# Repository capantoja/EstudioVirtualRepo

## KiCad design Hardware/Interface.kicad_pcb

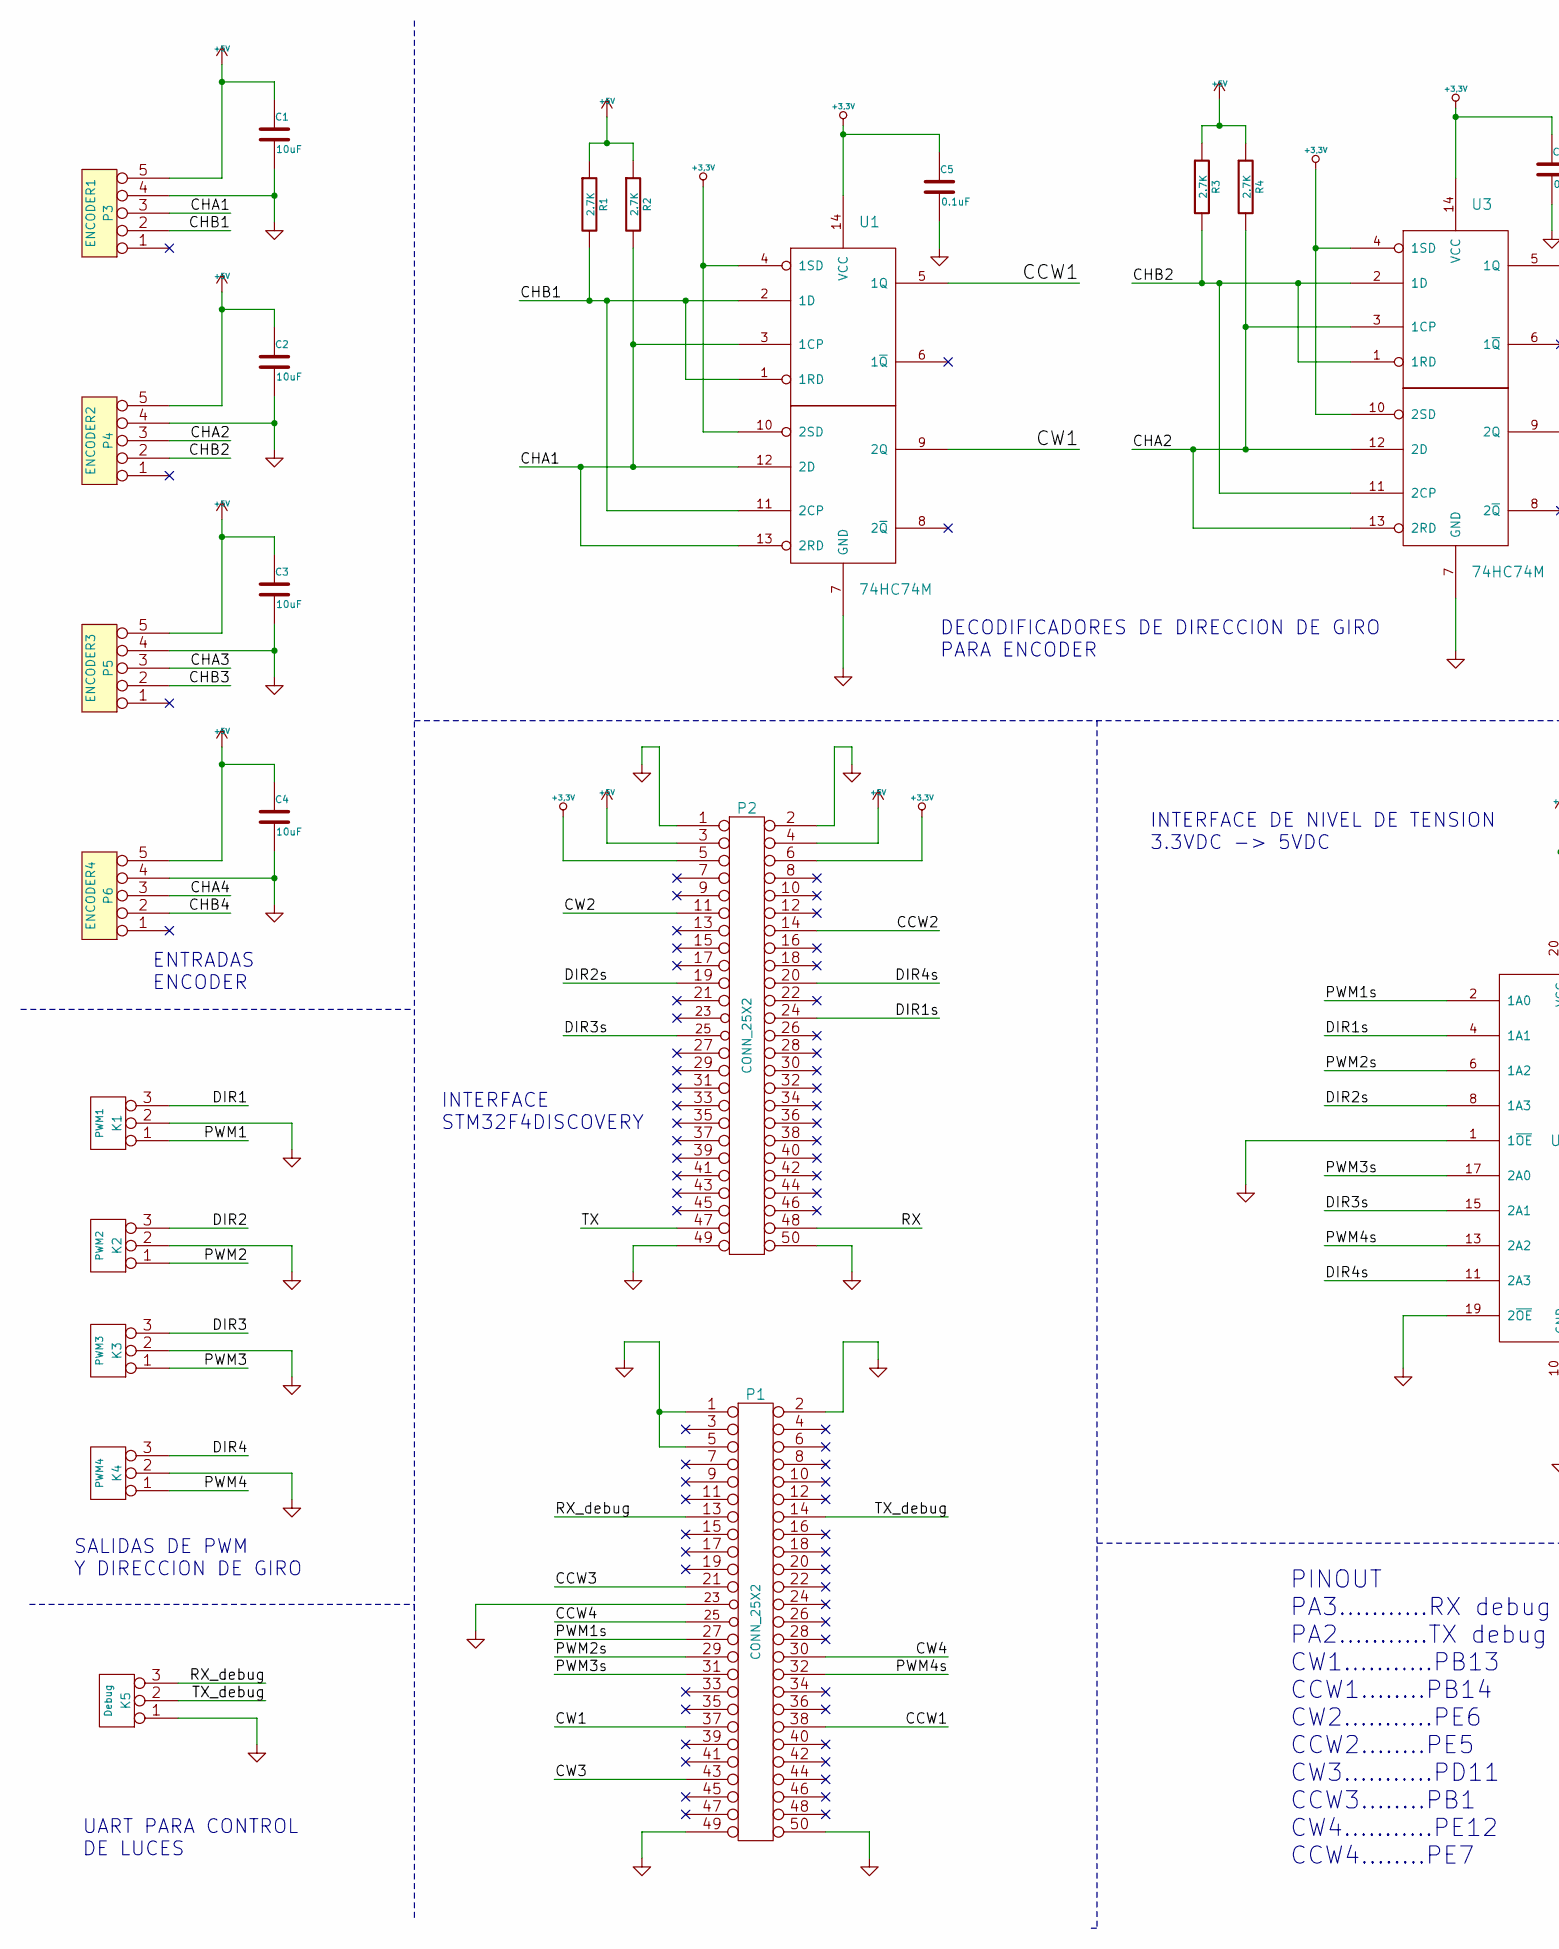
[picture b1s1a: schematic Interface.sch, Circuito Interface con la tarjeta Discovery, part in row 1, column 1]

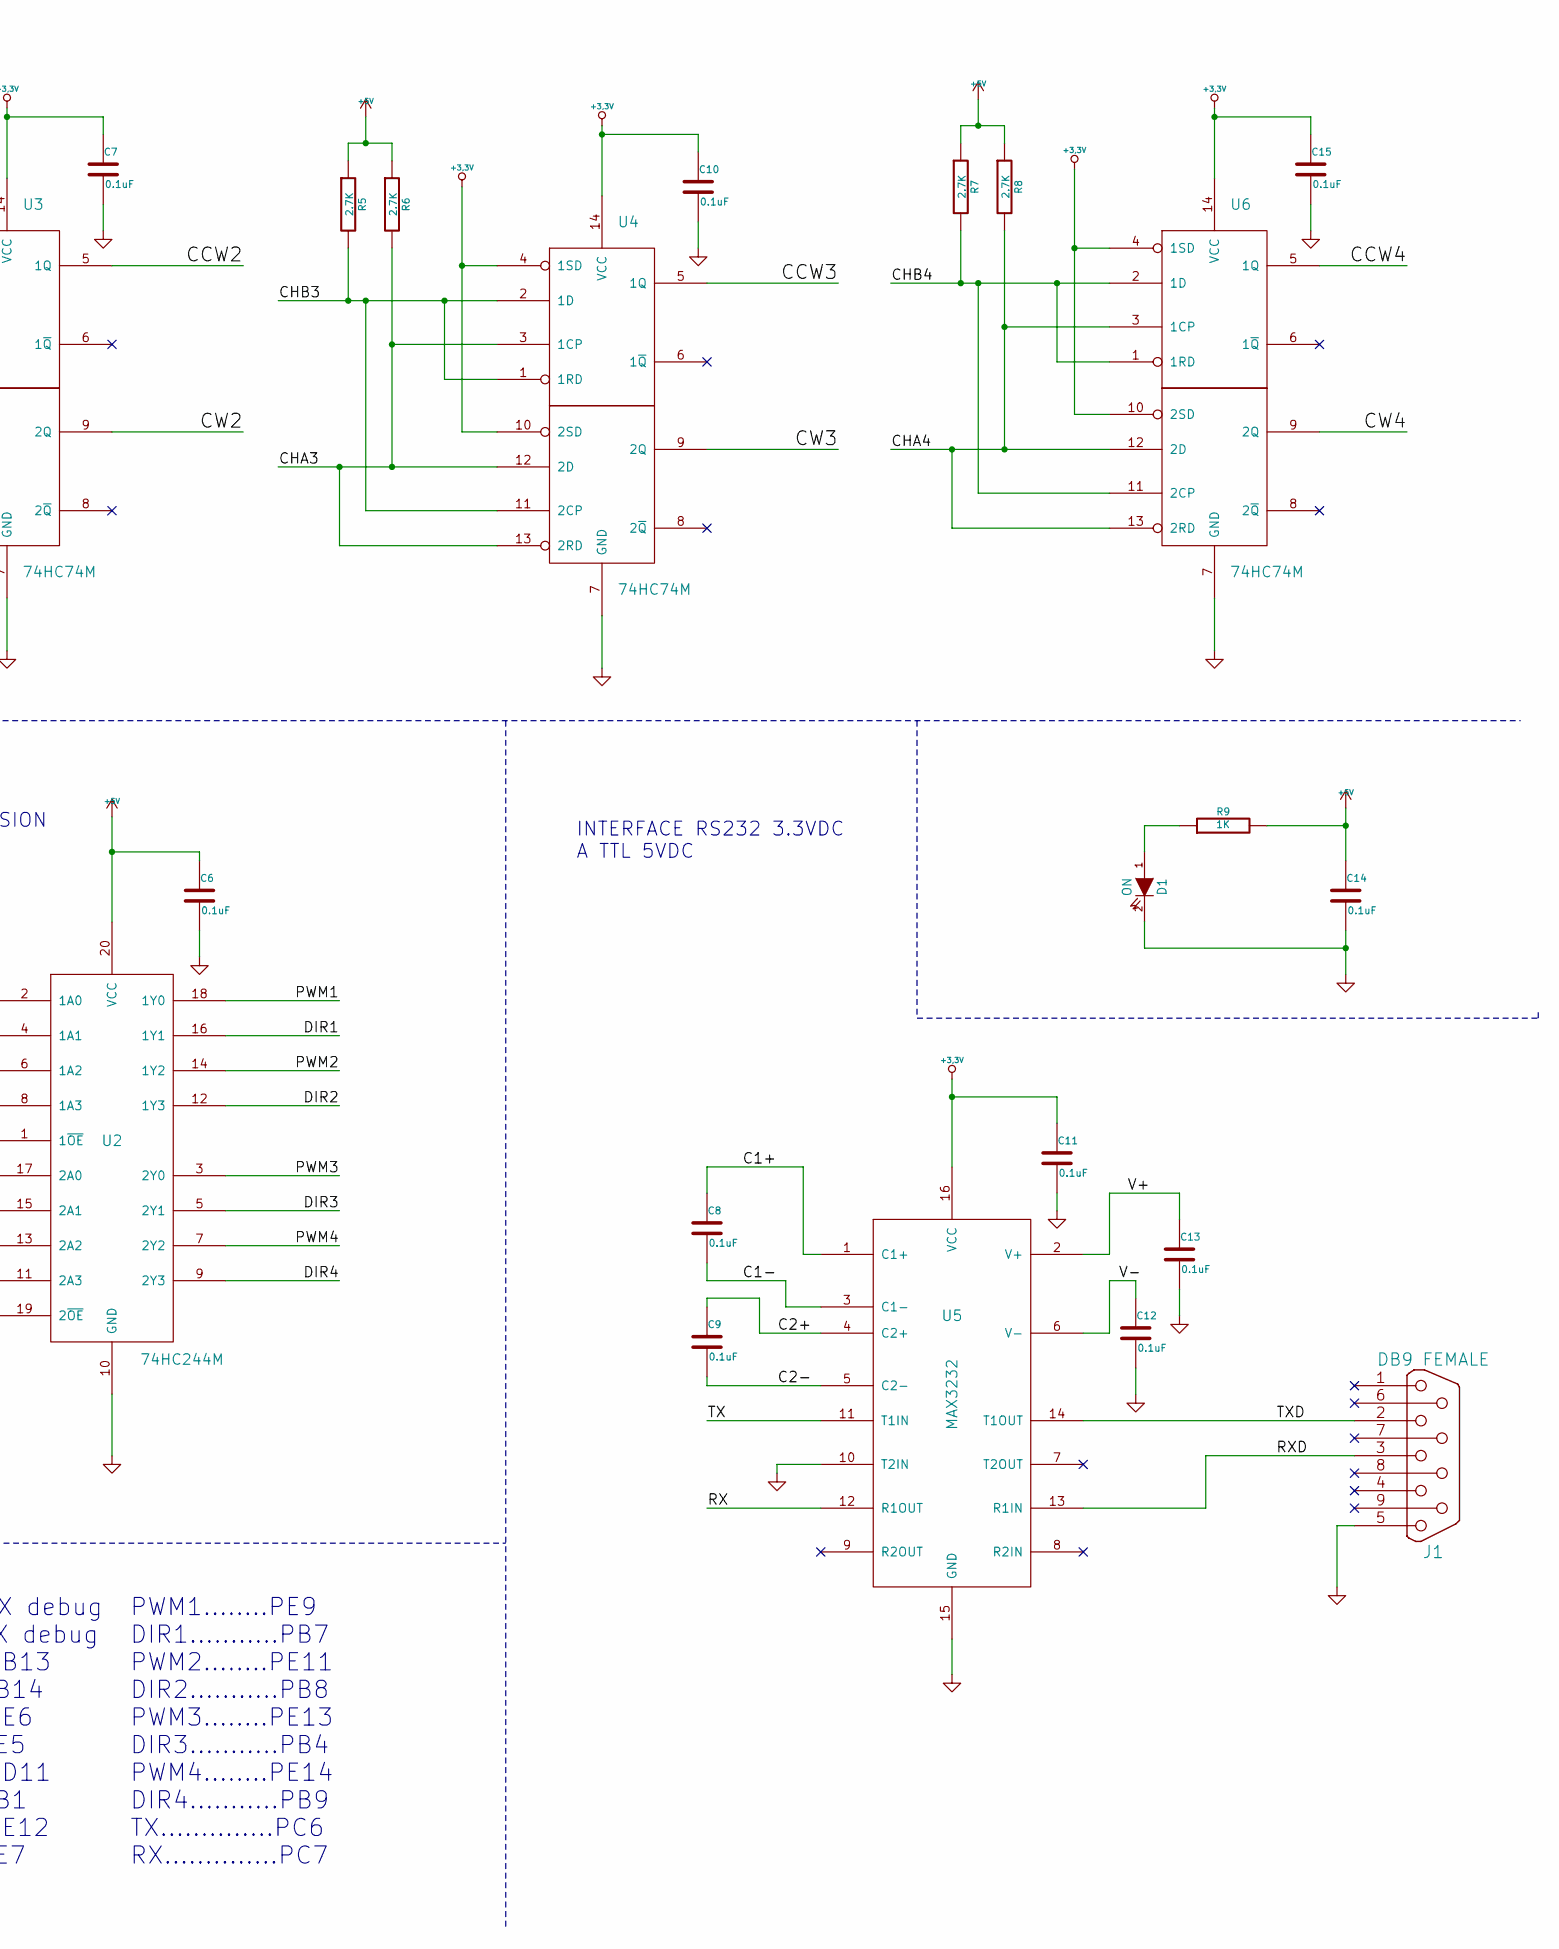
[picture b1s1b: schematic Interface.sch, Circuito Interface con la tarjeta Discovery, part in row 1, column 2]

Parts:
C1, C2, C3, C4: 10uF
C5, C6, C7, C8, C9, C10, C11, C12, C13, C14, C15: 0.1uF
D1: ON
J1: DB9 FEMALE
K1: PWM1
K2: PWM2
K3: PWM3
K4: PWM4
K5: Debug
P1, P2: CONN_25X2
P3: ENCODER1
P4: ENCODER2
P5: ENCODER3
P6: ENCODER4
R1, R2, R3, R4, R5, R6, R7, R8: 2.7K
R9: 1K
U1, U3, U4, U6: 74HC74M
U2: 74HC244M
U5: MAX3232

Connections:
+3.3V: C5.1, C7.1, C10.1, C11.1, C15.1, P2.5, P2.6, U1.4 (1SD), U1.10 (2SD), U1.14 (VCC), U3.4 (1SD), U3.10 (2SD), U3.14 (VCC), U4.4 (1SD), U4.10 (2SD), U4.14 (VCC), U5.16 (VCC), U6.4 (1SD), U6.10 (2SD), U6.14 (VCC)
+5V: C1.1, C2.1, C3.1, C4.1, C6.1, C14.1, P2.3, P2.4, P3.5, P4.5, P5.5, P6.5, R1.1, R2.1, R3.1, R4.1, R5.1, R6.1, R7.1, R8.1, R9.2, U2.20 (VCC)
/C1+: C8.1, U5.1 (C1+)
/C1-: C8.2, U5.3 (C1-)
/C2+: C9.1, U5.4 (C2+)
/C2-: C9.2, U5.5 (C2-)
/CCW1: P1.38, U1.5 (1Q)
/CCW2: P2.14, U3.5 (1Q)
/CCW3: P1.21, U4.5 (1Q)
/CCW4: P1.25, U6.5 (1Q)
/CHA1: P3.3, R2.2, U1.3 (1CP), U1.12 (2D), U1.13 (2RD)
/CHA2: P4.3, R4.2, U3.3 (1CP), U3.12 (2D), U3.13 (2RD)
/CHA3: P5.3, R6.2, U4.3 (1CP), U4.12 (2D), U4.13 (2RD)
/CHA4: P6.3, R8.2, U6.3 (1CP), U6.12 (2D), U6.13 (2RD)
/CHB1: P3.2, R1.2, U1.1 (1RD), U1.2 (1D), U1.11 (2CP)
/CHB2: P4.2, R3.2, U3.1 (1RD), U3.2 (1D), U3.11 (2CP)
/CHB3: P5.2, R5.2, U4.1 (1RD), U4.2 (1D), U4.11 (2CP)
/CHB4: P6.2, R7.2, U6.1 (1RD), U6.2 (1D), U6.11 (2CP)
/CW1: P1.37, U1.9 (2Q)
/CW2: P2.11, U3.9 (2Q)
/CW3: P1.43, U4.9 (2Q)
/CW4: P1.30, U6.9 (2Q)
/DIR1: K1.3, U2.16 (1Y1)
/DIR1s: P2.24, U2.4 (1A1)
/DIR2: K2.3, U2.12 (1Y3)
/DIR2s: P2.19, U2.8 (1A3)
/DIR3: K3.3, U2.5 (2Y1)
/DIR3s: P2.25, U2.15 (2A1)
/DIR4: K4.3, U2.9 (2Y3)
/DIR4s: P2.20, U2.11 (2A3)
/PWM1: K1.1, U2.18 (1Y0)
/PWM1s: P1.27, U2.2 (1A0)
/PWM2: K2.1, U2.14 (1Y2)
/PWM2s: P1.29, U2.6 (1A2)
/PWM3: K3.1, U2.3 (2Y0)
/PWM3s: P1.31, U2.17 (2A0)
/PWM4: K4.1, U2.7 (2Y2)
/PWM4s: P1.32, U2.13 (2A2)
/RX: P2.48, U5.12 (R1OUT)
/RXD: J1.3, U5.13 (R1IN)
/RX_debug: K5.3, P1.13
/TX: P2.47, U5.11 (T1IN)
/TXD: J1.2, U5.14 (T1OUT)
/TX_debug: K5.2 (PM), P1.14
/V+: C13.1, U5.2 (V+)
/V-: C12.1, U5.6 (V-)
GND: C1.2, C2.2, C3.2, C4.2, C5.2, C6.2, C7.2, C10.2, C11.2, C12.2, C13.2, C14.2, C15.2, D1.2 (K), J1.5, K1.2 (PM), K2.2 (PM), K3.2 (PM), K4.2 (PM), K5.1, P1.1, P1.2, P1.5, P1.23, P1.49, P1.50, P2.1, P2.2, P2.49, P2.50, P3.4, P4.4, P5.4, P6.4, U1.7 (GND), U2.1 (1~OE), U2.10 (GND), U2.19 (2~OE), U3.7 (GND), U4.7 (GND), U5.10 (T2IN), U5.15 (GND), U6.7 (GND)
unnamed: D1.1 (A), R9.1

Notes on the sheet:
PINOUT PA3...........RX debug PA2...........TX debug CW1...........PB13 CCW1........PB14 CW2...........PE6 CCW2........PE5 CW3...........PD11 CCW3........PB1 CW4...........PE12 CCW4........PE7
PWM1........PE9 DIR1...........PB7 PWM2........PE11 DIR2...........PB8 PWM3........PE13 DIR3...........PB4 PWM4........PE14 DIR4...........PB9 TX..............PC6 RX..............PC7
DECODIFICADORES DE DIRECCION DE GIRO PARA ENCODER
INTERFACE DE NIVEL DE TENSION 3.3VDC -> 5VDC
INTERFACE RS232 3.3VDC A TTL 5VDC
ENTRADAS ENCODER
SALIDAS DE PWM Y DIRECCION DE GIRO
UART PARA CONTROL DE LUCES
INTERFACE STM32F4DISCOVERY

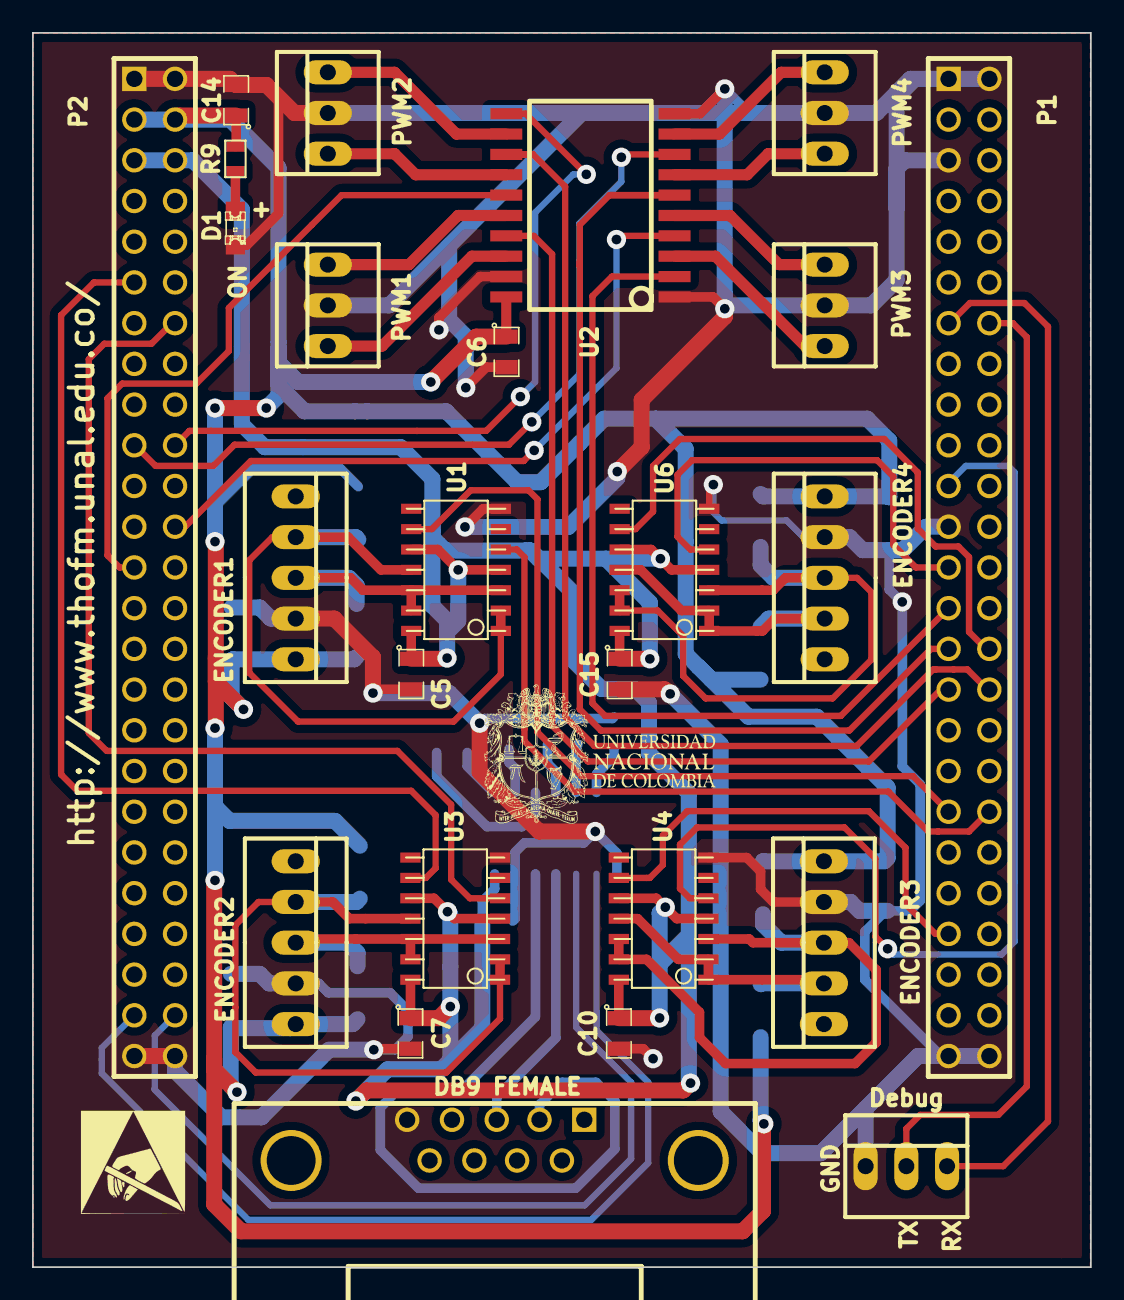
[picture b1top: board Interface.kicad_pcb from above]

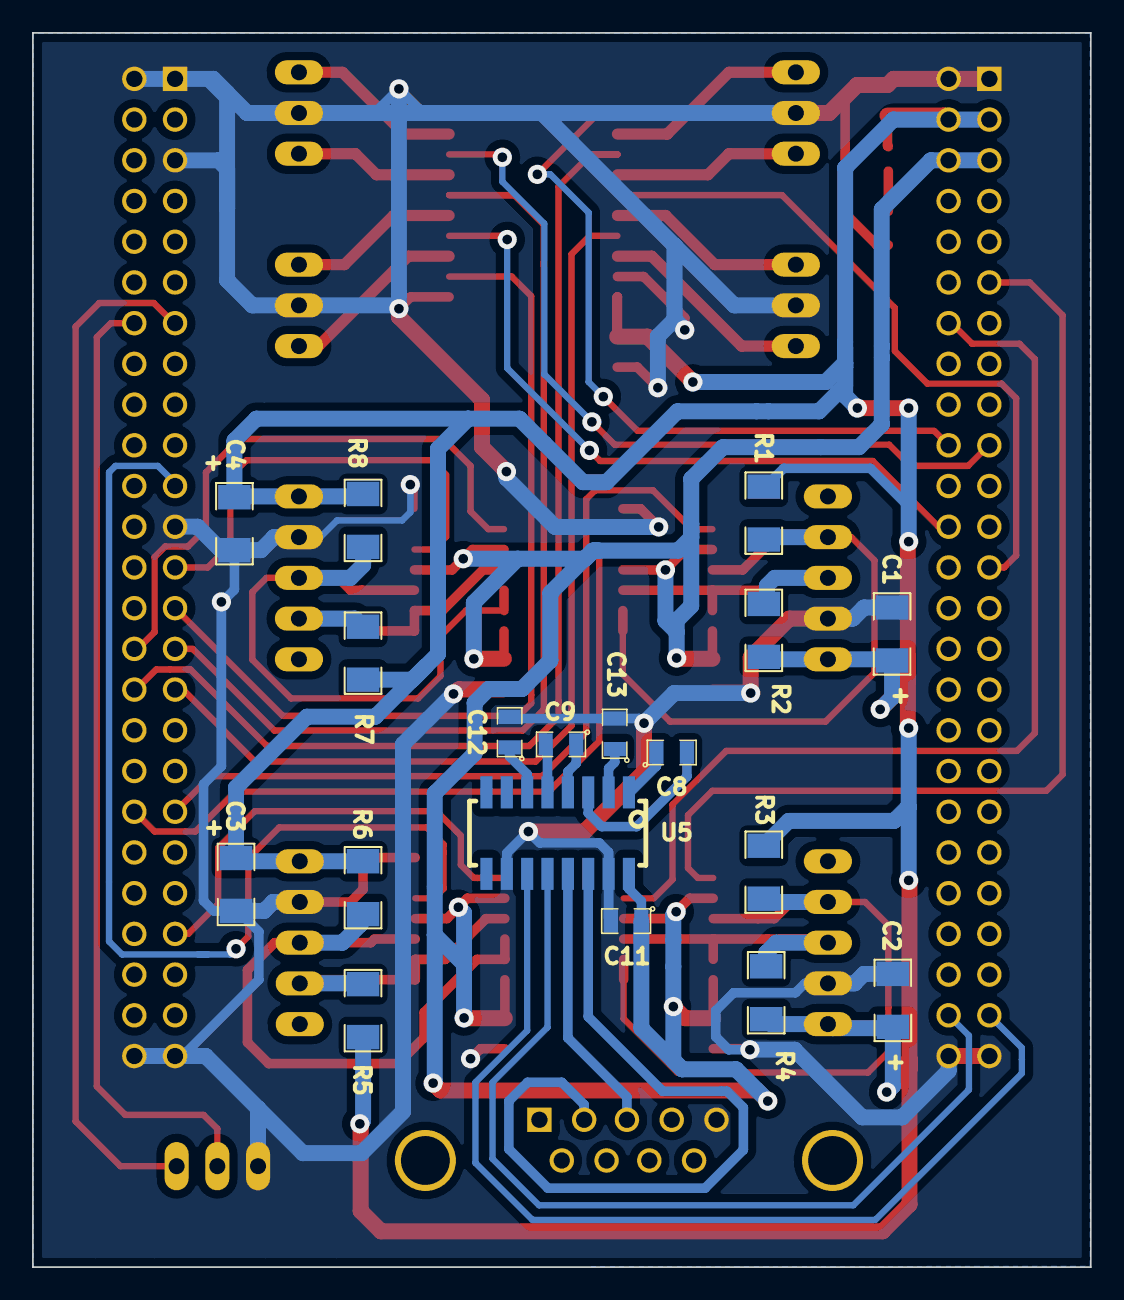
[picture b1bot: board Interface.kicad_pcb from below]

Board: 2 copper layers, 66.0 x 77.0 mm, 45 parts (18 on the bottom side), 48 nets.

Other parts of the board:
VAL: REF; ElectroStaticLogo
VAL#2: REF; UnalLogo

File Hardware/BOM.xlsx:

| UNIDADES DE PCBs: | 0
Cant requerida | Designator | Value | Descripción | Referencia Fabricante | Case | Web Link | Cantidad mínima de venta en distribuidor | Costo por un. Min. de venta | Costo por unidad | Unidades requeridas para 1 equipo | Unidades a comprar (para N PCB) | Costo de los componentes a comprar (DOLARES) | Costo de los componentes a comprar (PESOS)
COMPRAS INTERNACIONALES PCB
4 | C1,C2,C3,C4 | 10uF | Condensador de Tantalio de 10μF - 16V de montaje superficial. Tolerancia ± 10 % | CT1206 10UF16V | 1206 | http://www.sigmaelectronica.net/ct1206-10uf16v-p-1156.html | 1 | 348 | 348 | 4 |  |  | 1392
11 | C5,C6,C7,C8,C9,C10,C11,C12,C13,C14,C15 | 0.1uF | Condensador cerámico de 0.1μF - 50V de montaje superficial. Tamaño 0805 (2x1.2x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 | CC0805 0.1UF50 | 0805 | http://www.sigmaelectronica.net/cc0805-01uf50-p-1077.html | 10 | 58 | 58 | 11 |  |  | 638
1 | CON1 | JACK |  |  |  |  |  |  |  |  |  |  | 0
1 | J1 | DB9 | Conector DB- 9 Hembra para impreso de 9 pines. | DB9-H-IMP | - | http://www.sigmaelectronica.net/db9-h-imp-p-1578.html | 1 | 696 | 696 | 1 |  |  | 696
4 | K1,K2,K3,K4 | CONN 1X3 |  |  |  |  |  |  |  |  |  |  | 0
2 | P1,P2 | CONN 25X2 FEMALE |  |  |  |  |  |  |  |  |  |  | 0
4 | P3,P4,P5,P6 | CONN 1X5 |  |  |  |  |  |  |  |  |  |  | 0
8 | R1,R2,R3,R4,R5,R6,R7,R8 | 2.2K | Resistencia superficial de 2.2 KΩ, 1/10W | R0603 2.2K 5% | 0603 | http://www.sigmaelectronica.net/r0603-p-1675.html | 10 | 35 | 35 | 10 |  |  | 350
4 | U1,U3,U4,U6 | 74HC74M | 2 Flip-Flops tipo D con seteado y borrado. Tecnología High speed CMOS | 74HC74M | SOIC14 | http://www.sigmaelectronica.net/74hc74m-p-1138.html | 1 | 696 | 696 | 4 |  |  | 2784
1 | U5 | MAX3232 | RS232 DRIVER | MAX3232CSE | SO16 | http://www.sigmaelectronica.net/max3232cse-p-948.html | 1 | 3190 | 3190 | 1 |  |  | 3190
1 | U2 | 74HC244M | 8 buffers / tarnsmisores de línea / receptores de línea con salidas 3-state no 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 | 74HC244M | SOIC20 | http://www.sigmaelectronica.net/74hc244m-p-704.html | 1 | 1160 | 1160 | 1 |  |  | 1160
1 |  | ATSAM3N4A | Microcontrolador 32 bits | ATSAM3N4AA-AU | LQFP48 | http://www.sigmaelectronica.net/atsam3n4aa-p-1955.html | 1 | 15486 | 15486 | 1 |  | TOTAL | 10210
COMPRAS NACIONALES PCB
 |  |  |  |  |  |  | 1 | 0 | 0 | 1 | #REF! | NV | #REF!
 |  |  |  |  |  |  | 1 | 0 | 0 | 1 | #REF! | NV | #REF!
 |  |  |  |  |  |  | 1 | 0 | 0 | 1 | #REF! | NV | #REF!
 |  |  |  |  |  |  | 1 | 0 | 0 | 1 | #REF! | NV | #REF!
 |  |  |  |  |  |  | 1 | 0 | 0 | 1 | #REF! | NV | #REF!
 |  |  |  |  |  |  | 1 | 0 | 0 | 1 | #REF! | NV | #REF!
COMPRAS INTERNACIONALES ADICIONALES AL ENSAMBLE
 |  |  |  |  |  |  | 1 | 0.89 | 0.89 | 1 | 1 | 0.89 | NV
 |  |  |  |  |  |  | 1 | 0.52 | 0.52 | 1 | 1 | 0.52 | NV
 |  |  |  |  |  |  | 1 | 0.82 | 0.82 | 5 | 5 | 0
COMPRAS NACIONALES ADICIONALES AL ENSAMBLE
 |  |  |  |  |  |  |  |  |  |  |  | TOTAL USD | 1.4100000000000001
42 | TOTAL COMPONENTES POR UNIDAD: |  |  |  |  |  |  |  |  |  |  | TOTAL PESOS | #REF!
 | ÚLTIMA REVISIÓN DE STOCK: | 24/07/2014
 |  |  |  |  |  |  |  | UNIDAD PROMEDIO DOLARES: |  |  |  |  | #DIV/0!
 |  |  |  |  |  |  |  | UNIDAD PROMEDIO PESOS: |  |  |  |  | #REF!
 |  |  |  |  |  |  |  |  |  |  |  | Página 1 de 1

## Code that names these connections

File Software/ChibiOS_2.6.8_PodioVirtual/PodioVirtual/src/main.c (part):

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
  /* Inicializa los pines de lectura de los encoder */
  palSetPadMode(GPIOB, 13, PAL_MODE_INPUT);        // CW1
  palSetPadMode(GPIOB, 14, PAL_MODE_INPUT);        // CCW1
  palSetPadMode(GPIOE, 6,  PAL_MODE_INPUT);        // CW2
  palSetPadMode(GPIOE, 5,  PAL_MODE_INPUT);        // CCw2
  palSetPadMode(GPIOD, 11, PAL_MODE_INPUT);        // CW3
  palSetPadMode(GPIOB, 1,  PAL_MODE_INPUT);        // CCW3
  palSetPadMode(GPIOE, 12, PAL_MODE_INPUT);        // CW4
  palSetPadMode(GPIOE, 7,  PAL_MODE_INPUT);        // CCW4

  /* Inicializa MailBox */
  chMBInit(&mb1, b1, 8);
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
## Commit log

2015-03-09 :boom::camel: Added .gitattributes & .gitignore files
2015-03-09 Project add
2015-06-07 Datasheet file add
2015-06-07 Documentacion file add
2015-06-07 Gerber file add
2015-06-07 Hardware project add
2015-06-07 Software project chibios add
2015-06-07 BOM add
2015-06-07 BOM pdf add
